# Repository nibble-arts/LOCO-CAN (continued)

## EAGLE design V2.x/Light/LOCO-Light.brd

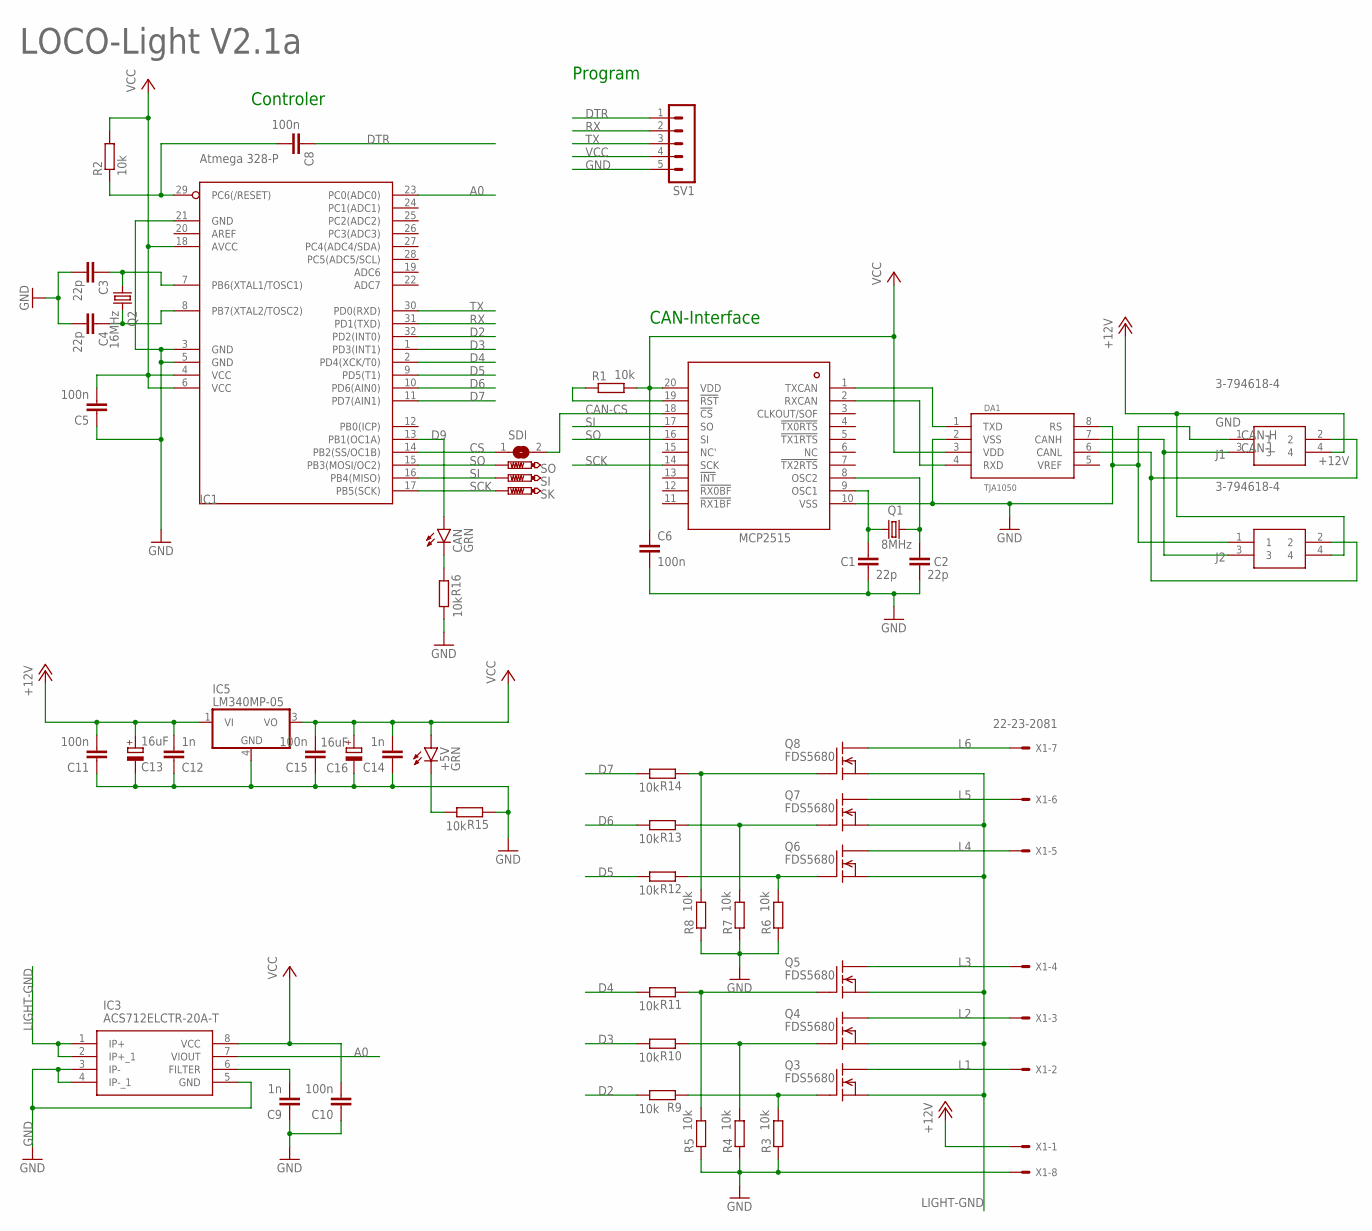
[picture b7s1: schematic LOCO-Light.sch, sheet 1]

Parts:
+5V: GRN; CHIP-LED0603
C1, C2, C3, C4: 22p; C0402K
C5, C6, C8, C10, C11, C15: 100n; C0402K
C9, C12, C14: 1n; C0402K
C13, C16: 16uF; A/3216-18W
CAN: GRN; CHIP-LED0603
DA1: TJA1050; SO08
IC1: Atmega 328-P; TQFP32-08
IC2: MCP2515; TSSOP20
IC3: ACS712ELCTR-20A-T; SOIC127P600X175-8N
IC5: LM340MP-05; SOT223
J1, J2: 3-794618-4; SHDRRA4W102P300_2X2_686X892X73
Q1: 8MHz; HC49/S
Q2: 16MHz; HC49/S
Q3, Q4, Q5, Q6, Q7, Q8: FDS5680; SO-8
R1, R2, R3, R4, R5, R6, R7, R8, R9, R10, R11, R12, R13, R14, R15, R16: 10k; R0603
SDI: SJ
SI: PTR1B1,27; B1,27
SK: PTR1B1,27; B1,27
SO: PTR1B1,27; B1,27
SV1: MA05-1
X1: 22-23-2081

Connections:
+12V: C11.2, C12.2, C13.+, IC5.1 (VI), J1.4, J2.4, X1.1
A0: IC1.23 (PC0(ADC0)), IC3.7 (VIOUT)
CAN-CS: IC2.18 (!CS), SDI.2
CAN-H: DA1.7 (CANH), J1.3, J2.3
CAN-L: DA1.6 (CANL), J1.2, J2.2
CAN-OCC1: C1.1, IC2.9 (OSC1), Q1.1
CAN-OCC2: C2.1, IC2.8 (OSC2), Q1.2
CS: IC1.14 (PB2(SS/OC1B)), SDI.1
D2: IC1.32 (PD2(INT0)), R9.2
D3: IC1.1 (PD3(INT1)), R10.2
D4: IC1.2 (PD4(XCK/T0)), R11.2
D5: IC1.9 (PD5(T1)), R12.2
D6: IC1.10 (PD6(AIN0)), R13.2
D7: IC1.11 (PD7(AIN1)), R14.2
D9: CAN.A, IC1.13 (PB1(OC1A))
DTR: C8.1, SV1.1
GND: C1.2, C2.2, C3.2, C4.2, C5.1, C6.2, C9.1, C10.1, C11.1, C12.1, C13.-, C14.1, C15.1, C16.-, DA1.2 (VSS), DA1.8 (RS), IC1.3 (GND), IC1.5 (GND), IC1.21 (GND), IC2.10 (VSS), IC3.3 (IP-), IC3.4 (IP-_1), IC3.5 (GND), IC5.4 (GND), J1.1, J2.1, R3.1, R4.1, R5.1, R6.1, R7.1, R8.1, R15.1, R16.2, SV1.5, X1.8
L1: Q3.5 (D), Q3.6 (D), Q3.7 (D), Q3.8 (D), X1.2
L2: Q4.5 (D), Q4.6 (D), Q4.7 (D), Q4.8 (D), X1.3
L3: Q5.5 (D), Q5.6 (D), Q5.7 (D), Q5.8 (D), X1.4
L4: Q6.5 (D), Q6.6 (D), Q6.7 (D), Q6.8 (D), X1.5
L5: Q7.5 (D), Q7.6 (D), Q7.7 (D), Q7.8 (D), X1.6
L6: Q8.5 (D), Q8.6 (D), Q8.7 (D), Q8.8 (D), X1.7
LIGHT-GND: IC3.1 (IP+), IC3.2 (IP+_1), Q3.1 (S), Q3.2 (S), Q3.3 (S), Q4.1 (S), Q4.2 (S), Q4.3 (S), Q5.1 (S), Q5.2 (S), Q5.3 (S), Q6.1 (S), Q6.2 (S), Q6.3 (S), Q7.1 (S), Q7.2 (S), Q7.3 (S), Q8.1 (S), Q8.2 (S), Q8.3 (S)
unnamed: C9.2, IC3.6 (FILTER)
unnamed: Q3.4 (G), R3.2, R9.1
unnamed: Q4.4 (G), R4.2, R10.1
unnamed: Q5.4 (G), R5.2, R11.1
unnamed: Q6.4 (G), R6.2, R12.1
unnamed: IC2.19 (!RST), R1.1
unnamed: Q7.4 (G), R7.2, R13.1
unnamed: Q8.4 (G), R8.2, R14.1
unnamed: CAN.C, R16.1
unnamed: C3.1, IC1.7 (PB6(XTAL1/TOSC1)), Q2.1
unnamed: C4.1, IC1.8 (PB7(XTAL2/TOSC2)), Q2.2
unnamed: +5V.C, R15.2
unnamed: C8.2, IC1.29 (PC6(/RESET)), R2.1
RX: IC1.31 (PD1(TXD)), SV1.2
RXCAN: DA1.4 (RXD), IC2.2 (RXCAN)
SCK: IC1.17 (PB5(SCK)), IC2.14 (SCK), SK.TP
SI: IC1.16 (PB4(MISO)), IC2.17 (SO), SI.TP
SO: IC1.15 (PB3(MOSI/OC2)), IC2.16 (SI), SO.TP
TX: IC1.30 (PD0(RXD)), SV1.3
TXCAN: DA1.1 (TXD), IC2.1 (TXCAN)
VCC: +5V.A, C5.2, C6.1, C10.2, C14.2, C15.2, C16.+, DA1.3 (VDD), IC1.4 (VCC), IC1.6 (VCC), IC1.18 (AVCC), IC2.20 (VDD), IC3.8 (VCC), IC5.3 (VO), R1.2, R2.2, SV1.4

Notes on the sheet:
Program
CAN-Interface
Controler
LOCO-Light V2.1a

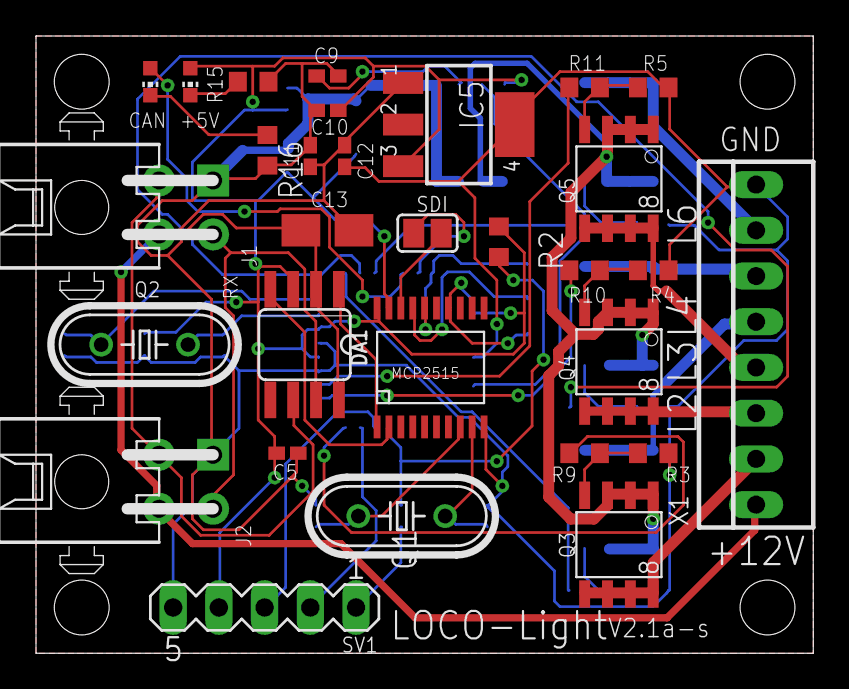
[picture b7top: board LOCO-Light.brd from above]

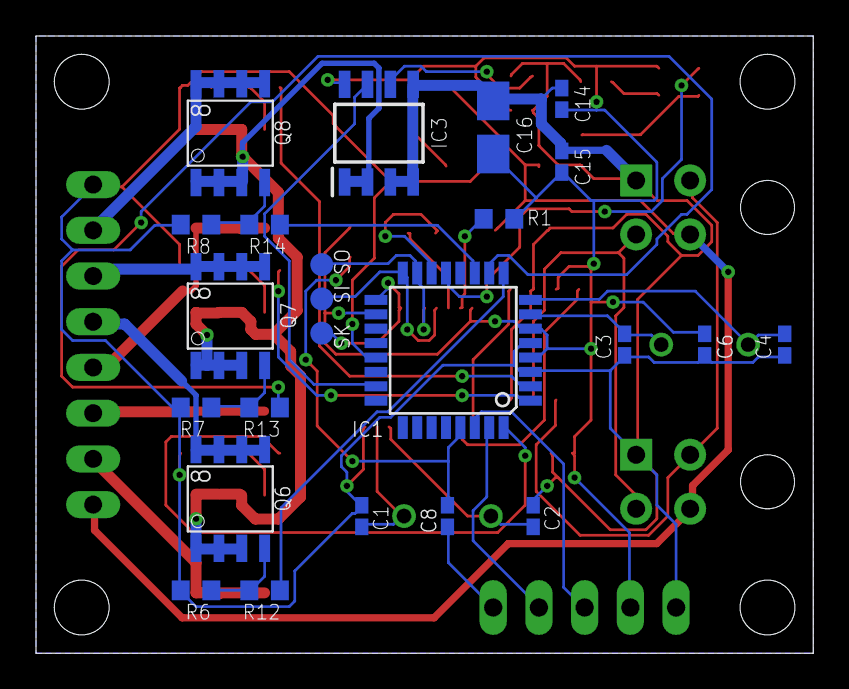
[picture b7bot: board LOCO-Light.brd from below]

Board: 2 copper layers, 43.2 x 34.3 mm, 54 parts (24 on the bottom side), 45 nets.

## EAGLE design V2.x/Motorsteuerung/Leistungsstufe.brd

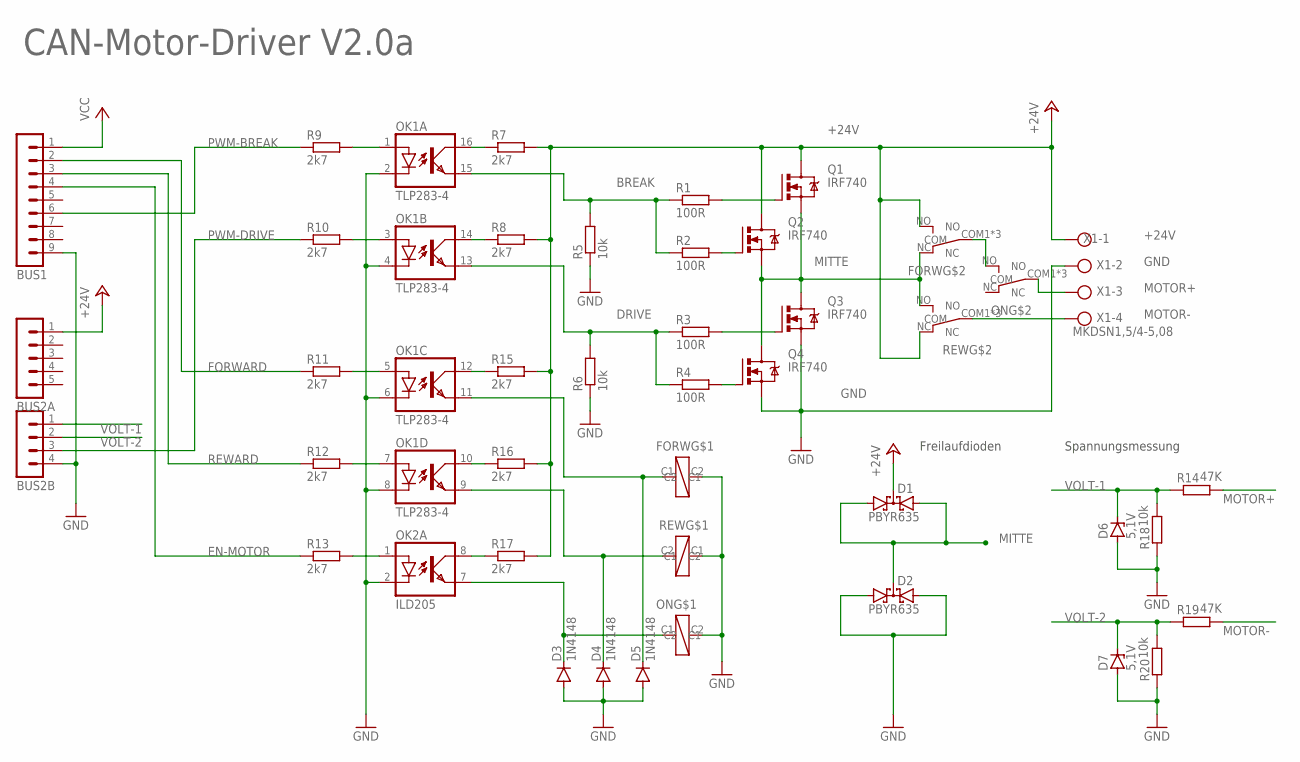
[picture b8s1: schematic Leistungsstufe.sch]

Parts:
BUS1: MA09-1
BUS2A: MA05-1
BUS2B: MA04-1
D1, D2: PBYR635; SOT82S
D3, D4, D5: 1N4148; SOD323-R
D6, D7: 5,1V; SOD80C
FORW: FRA2C-2
OK1: TLP283-4; MINI-FLAT-16
OK2: ILD205; SOIC08
ON: FRA2C-2
Q1, Q2, Q3, Q4: IRF740; TO220BV
R1, R2, R3, R4: 100R; R0805
R5, R6: 10k; R0805
R7, R8, R9, R10, R11, R12, R13, R15, R16, R17: 2k7; R0805
R14, R19: 47K; MINI_MELF-0102W
R18, R20: 10k; MINI_MELF-0102W
REW: FRA2C-2
X1: MKDSN1,5/4-5,08

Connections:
+24V: BUS2A.1, D1.C, FORW.NO, Q1.D, Q2.D, R7.2, R8.2, R15.2, R16.2, R17.2, REW.NC, X1.1
BREAK: OK1.15 (EMIT), R1.1, R2.1, R5.2
DRIVE: OK1.13 (EMIT), R3.1, R4.1, R6.2
EN-MOTOR: BUS1.4, R13.1
FORWARD: BUS1.2, R11.1
GND: BUS1.9, BUS2B.4, D2.A1, D2.A2, D3.A, D4.A, D5.A, D6.A, D7.A, FORW.C2, OK1.2 (C), OK1.4 (C), OK1.6 (C), OK1.8 (C), OK2.2 (C), ON.C2, Q3.S, Q4.S, R5.1, R6.1, R18.1, R20.1, REW.C1, X1.2
M+SWITCH: FORW.COM1 (COM), FORW.COM2 (COM), FORW.COM3 (COM), ON.NO
MITTE: D1.A1, D1.A2, D2.C, FORW.NC, Q1.S, Q2.S, Q3.D, Q4.D, REW.NO
MOTOR+: ON.COM1 (COM), ON.COM2 (COM), ON.COM3 (COM), R14.2, X1.3
MOTOR-: R19.2, REW.COM1 (COM), REW.COM2 (COM), REW.COM3 (COM), X1.4
unnamed: Q2.G, R2.2
unnamed: Q3.G, R3.2
unnamed: Q4.G, R4.2
unnamed: Q1.G, R1.2
unnamed: OK1.3 (A), R10.2
unnamed: D5.C, FORW.C1, OK1.11 (EMIT)
unnamed: D4.C, OK1.9 (EMIT), REW.C2
unnamed: D3.C, OK2.7 (EMIT), ON.C1
unnamed: OK1.16 (COL), R7.1
unnamed: OK1.14 (COL), R8.1
unnamed: OK1.1 (A), R9.2
unnamed: OK1.5 (A), R11.2
unnamed: OK1.7 (A), R12.2
unnamed: OK2.1 (A), R13.2
unnamed: OK1.10 (COL), R16.1
unnamed: OK2.8 (COL), R17.1
unnamed: OK1.12 (COL), R15.1
PWM-BREAK: BUS1.6, R9.1
PWM-DRIVE: BUS2B.3, R10.1
REWARD: BUS1.3, R12.1
VCC: BUS1.1
VOLT-1: BUS2B.1, D6.C, R14.1, R18.2
VOLT-2: BUS2B.2, D7.C, R19.1, R20.2

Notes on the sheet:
Freilaufdioden
Spannungsmessung
CAN-Motor-Driver V2.0a

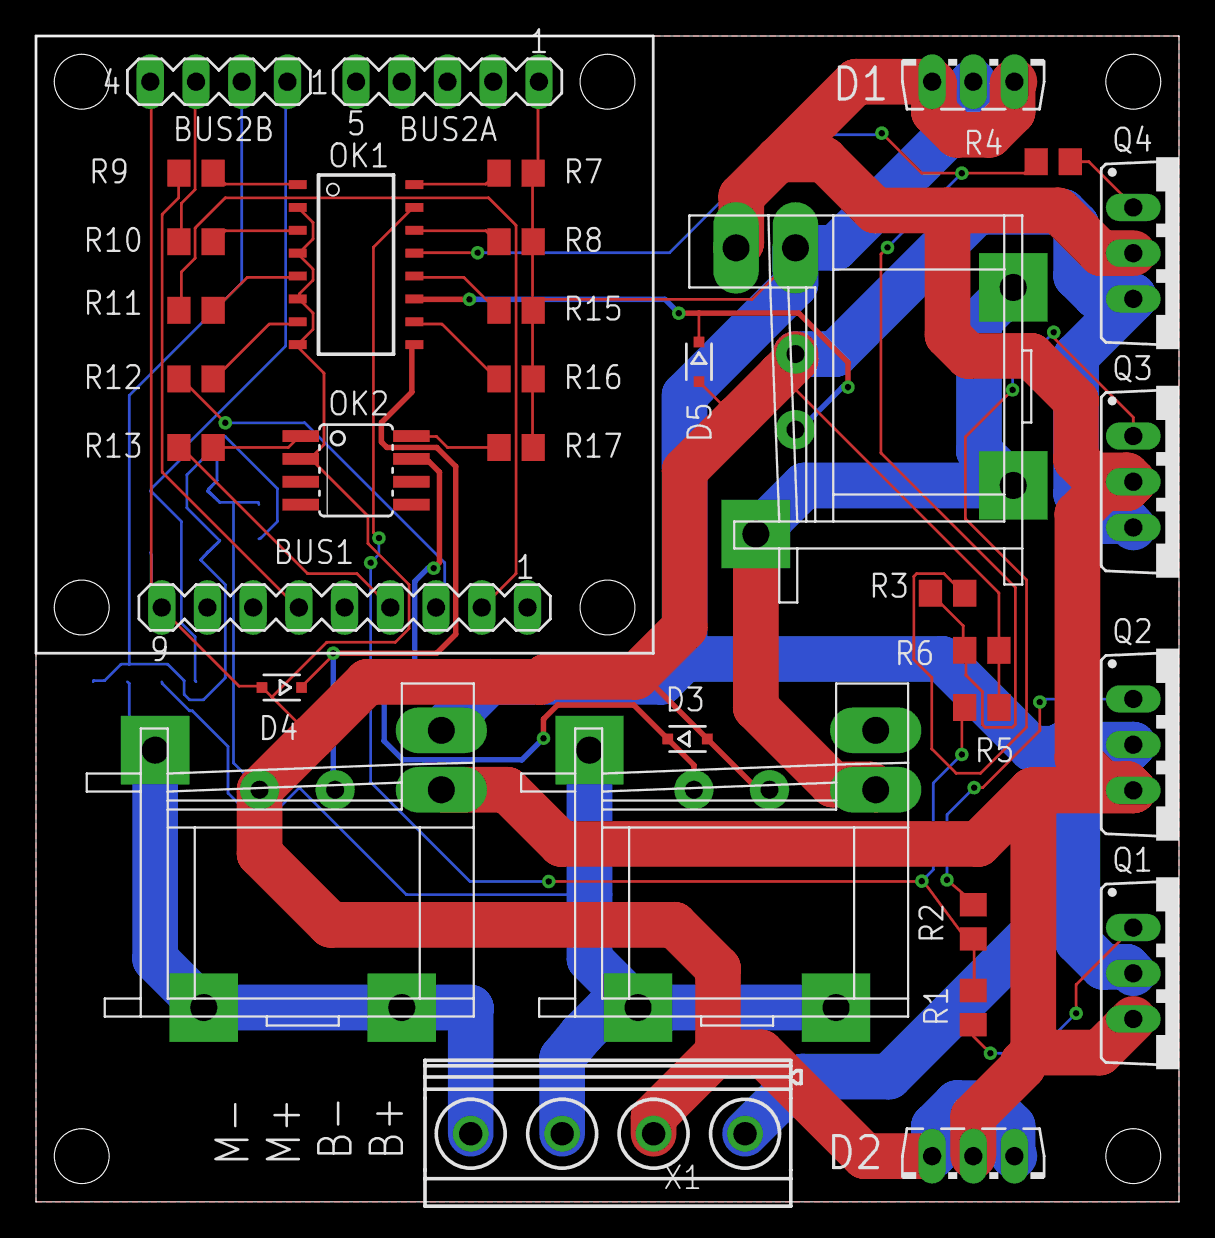
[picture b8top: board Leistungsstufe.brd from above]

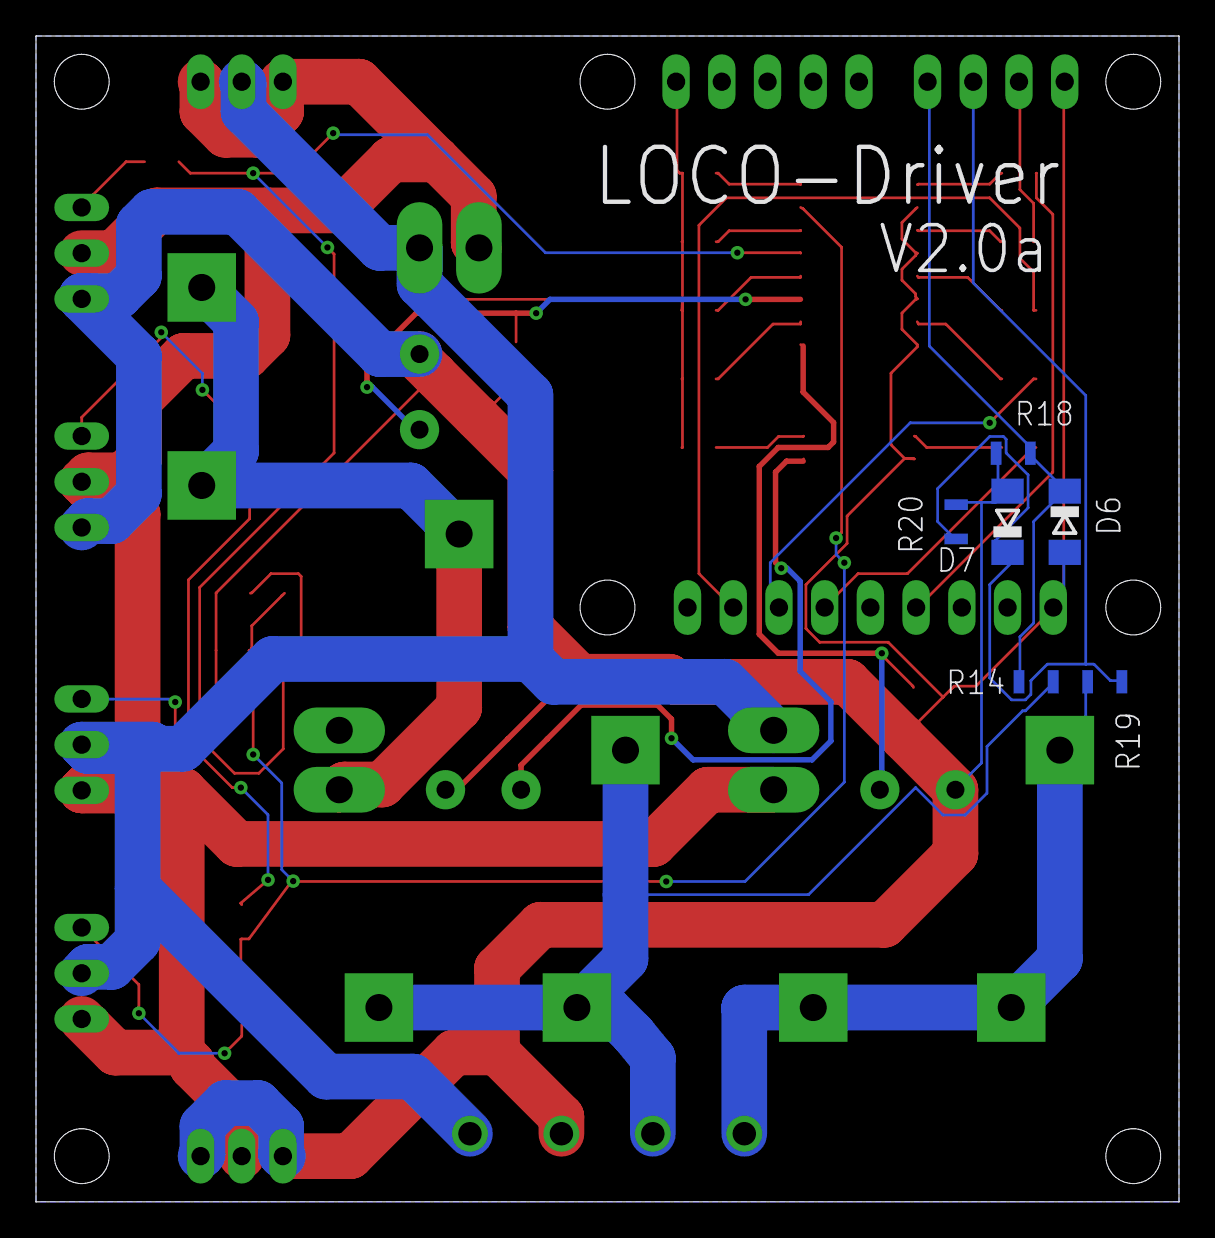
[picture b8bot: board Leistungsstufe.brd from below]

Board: 2 copper layers, 63.5 x 64.8 mm, 40 parts (6 on the bottom side), 32 nets.
